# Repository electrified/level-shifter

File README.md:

## Board to interface 3.3v FPGA board with RC2014

## BOM

5x SN74CB3T3245

LD1117S33TR

100nF 0805 capacitors

10μF 0805 capacitors

## License

Copyright Ed Brindley 2020.

This source describes Open Hardware and is licensed under the CERN-OHL-P v2
You may redistribute and modify this documentation and make products using it under the terms of the CERN-OHL-P v2 (https:/cern.ch/cern-ohl). This documentation is distributed WITHOUT ANY EXPRESS OR IMPLIED WARRANTY, INCLUDING OF MERCHANTABILITY, SATISFACTORY QUALITY AND FITNESS FOR A PARTICULAR PURPOSE. Please see the CERN-OHL-P v2 for applicable conditions

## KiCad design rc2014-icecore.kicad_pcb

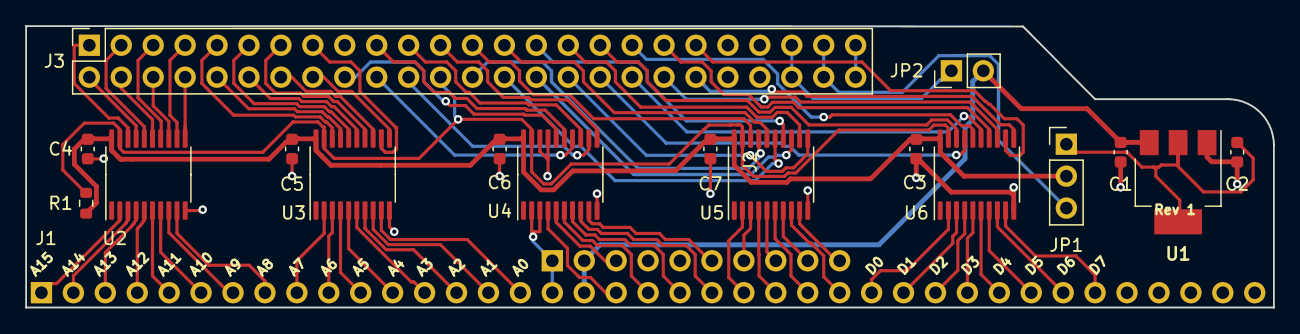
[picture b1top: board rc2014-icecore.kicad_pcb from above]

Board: 2 copper layers, 99.3 x 22.4 mm, 19 parts (0 on the bottom side), 83 nets.

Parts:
C1: 100nF; C_0603_1608Metric
C2: 10uF; C_0603_1608Metric
C3, C4, C5, C6, C7: C; C_0603_1608Metric
J1: Conn_01x39; PinHeader_1x39_P2.54mm_Vertical_NoSilk
J2: Conn_01x10; PinHeader_1x10_P2.54mm_Vertical_NoSilk
J3: Conn_02x25_Odd_Even; PinSocket_2x25_P2.54mm_Vertical
JP1: Ext Power; PinHeader_1x03_P2.54mm_Vertical
JP2: Jumper; PinHeader_1x02_P2.54mm_Vertical
R1: R; R_0603_1608Metric
U1: LM1117-3.3; SOT-223-3_TabPin2
U2, U3, U4, U5, U6: SN74CB3T3245; TSSOP-20_4.4x6.5mm_P0.65mm

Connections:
+3V3: C3.1, C4.1, C5.1, C6.1, C7.1, JP1.2, R1.1, U2.20, U3.20, U4.20, U5.20, U6.20
+5V: C1.1, J1.18, J2.2, JP2.2, U1.3
//IORQ: J1.26, U5.8
//RD: J1.25, U5.6
//RESET: J1.20, U4.6
//WR: J1.24, U5.4
/A0: J1.16, U3.9
/A1: J1.15, U3.8
/A2: J1.14, U3.7
/A3: J1.13, U3.6
/A4: J1.12, U3.5
/A5: J1.11, U3.4
/A6: J1.10, U3.3
/A7: J1.9, U3.2
/A8: J1.8, U2.9
/A9: J1.7, U2.8
/A10: J1.6, U2.7
/A11: J1.5, U2.6
/A12: J1.4, U2.5
/A13: J1.3, U2.4
/A14: J1.2, U2.3
/A15: J1.1, U2.2
/BUSACK: J2.6, U4.9
/CLK: J1.21, U4.7
/D0: J1.27, U6.2
/D1: J1.28, U6.3
/D2: J1.29, U6.4
/D3: J1.30, U6.5
/D4: J1.31, U6.6
/D5: J1.32, U6.7
/D6: J1.33, U6.8
/D7: J1.34, U6.9
/FPGA_VCC: J3.47, J3.48, JP1.3
/INT: J1.22, U4.8
/M1: J1.19, U4.4
/MREQ: J1.23, U5.2
/P0: J3.1, U2.18
/P1: J3.2, U2.17
/P2: J3.3, U2.16
/P3: J3.4, U2.15
/P4: J3.5, U2.14
/P5: J3.6, U2.13
/P6: J3.7, U2.12
/P7: J3.8, U2.11
/P8: J3.9, U3.18
/P9: J3.10, U3.17
/P10: J3.11, U3.16
/P11: J3.12, U3.15
/P12: J3.13, U3.14
/P13: J3.14, U3.13
/P14: J3.15, U3.12
/P15: J3.16, U3.11
/P17: J3.18, U4.16
/P18: J3.19, U4.15
/P19: J3.20, U4.14
/P20: J3.21, U4.13
/P21: J3.22, U4.12
/P22: J3.23, U4.11
/P23: J3.24, R1.2, U2.19, U3.19, U4.19, U5.19, U6.19
/P24: J3.25, U5.18
/P25: J3.26, U5.17
/P26: J3.27, U5.16
/P27: J3.28, U5.15
/P28: J3.29, U5.14
/P29: J3.30, U5.13
/P30: J3.31, U5.12
/P31: J3.32, U5.11
/P48: J3.33, U6.18
/P49: J3.34, U6.17
/P50: J3.35, U6.16
/P51: J3.36, U6.15
/P52: J3.37, U6.14
/P53: J3.38, U6.13
/P54: J3.39, U6.12
/P55: J3.40, U6.11
/~BUSREQ: J2.8, U5.5
/~HALT: J2.7, U5.3
/~NMI: J2.10, U5.9
/~RFSH: J2.3, U4.5
/~WAIT: J2.9, U5.7
GND: C1.2, C2.2, C3.2, C4.2, C5.2, C6.2, C7.2, J1.17, J2.1, J3.49, J3.50, U1.1, U2.10, U3.10, U4.2, U4.3, U4.10, U4.17, U4.18, U5.10, U6.10
unnamed: C2.1, JP1.1, U1.2
unnamed: J3.45, J3.46, JP2.1

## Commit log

2020-10-20 WIP of level shifter
2020-10-22 Rev 1 as sent to JLCPCB
2021-05-10 Remove non-relevant PDF datasheets
2023-01-29 Update for Kicad 6
2023-01-29 Further Kicad 6 updates
2023-09-17 Update to kicad 7
